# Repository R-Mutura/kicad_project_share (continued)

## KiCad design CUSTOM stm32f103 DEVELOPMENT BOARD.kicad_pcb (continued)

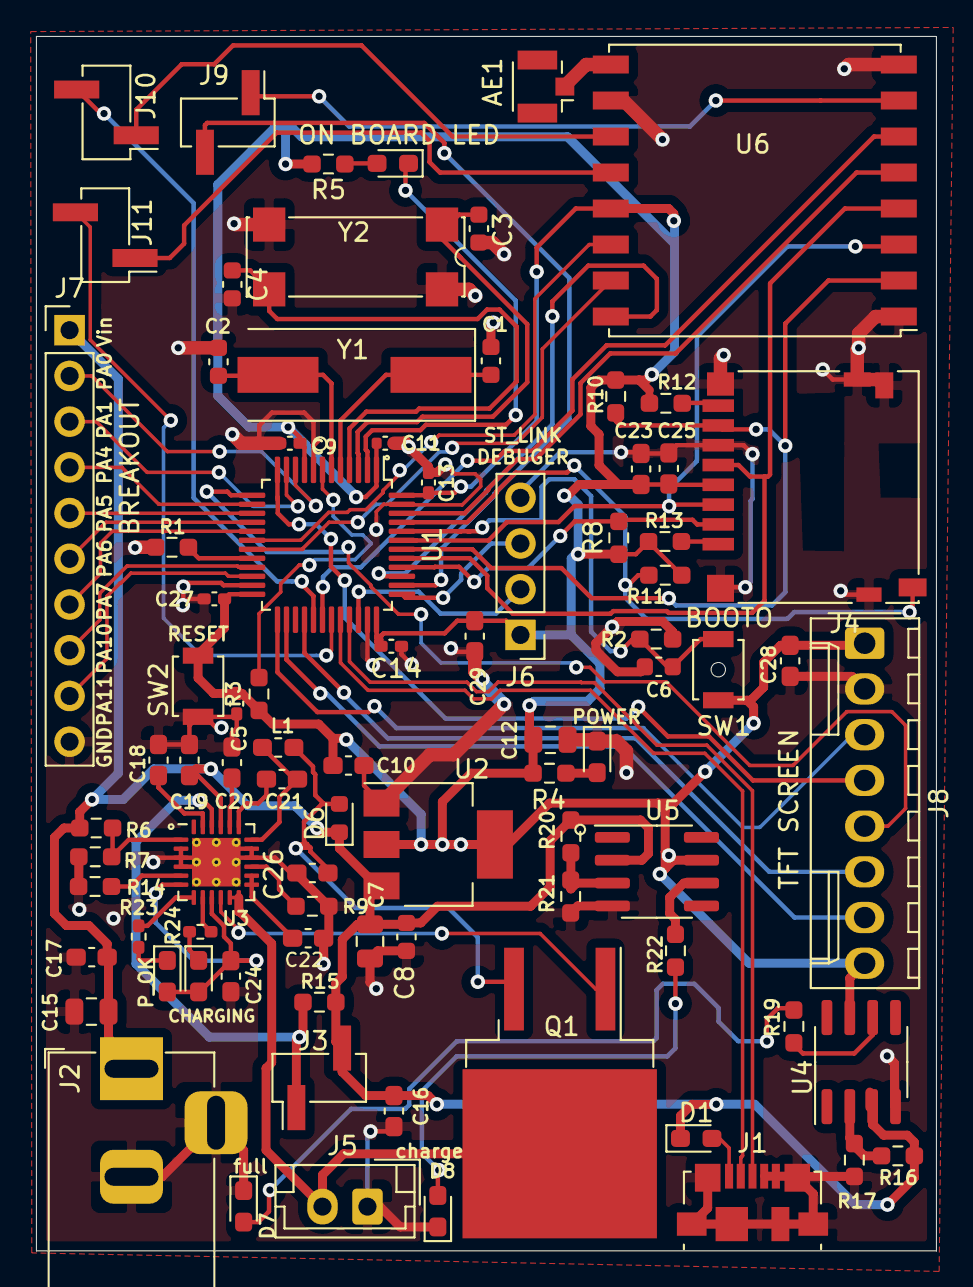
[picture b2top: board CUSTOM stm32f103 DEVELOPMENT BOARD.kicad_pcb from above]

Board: 2 copper layers, 50.0 x 67.5 mm, 84 parts (0 on the bottom side), 73 nets.

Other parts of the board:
ON BOARD LED: ON_BOARD_LED; D_0603_1608Metric_Pad1.05x0.95mm_HandSolder
POWER: POWER_LED; D_0603_1608Metric_Pad1.05x0.95mm_HandSolder

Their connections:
GND: POWER.1; also elsewhere on the board
unnamed 29: POWER.2; also elsewhere on the board
unnamed 30: ON BOARD LED.2; also elsewhere on the board
PC13: ON BOARD LED.1; also elsewhere on the board

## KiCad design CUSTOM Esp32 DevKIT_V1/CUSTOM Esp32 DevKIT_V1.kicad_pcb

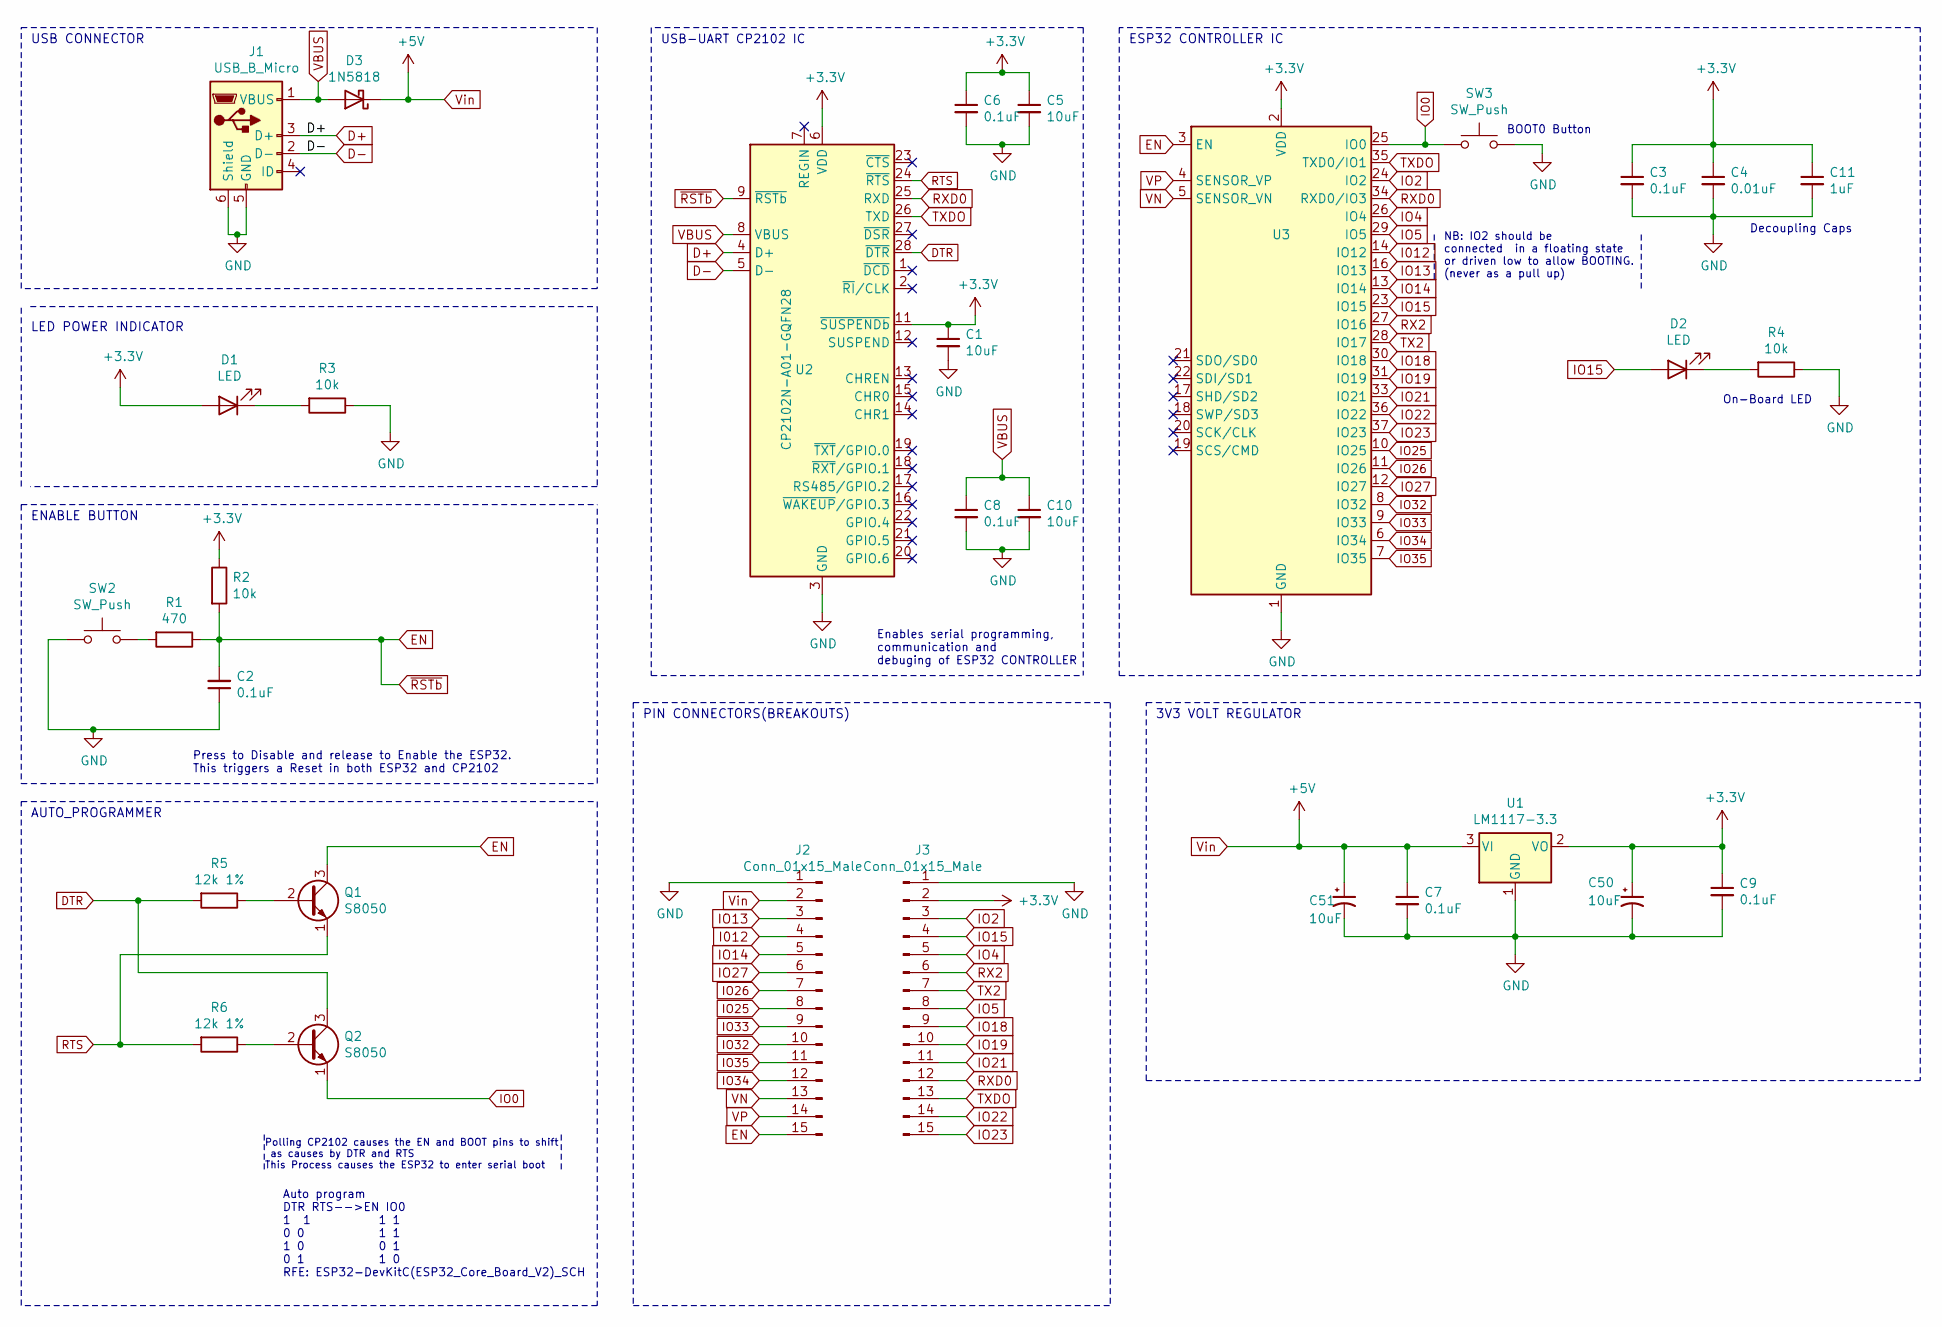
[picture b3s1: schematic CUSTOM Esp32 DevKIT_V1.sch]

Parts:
C1, C5, C10: 10uF; C_0402_1005Metric
C2, C3, C6, C7, C8, C9: 0.1uF; C_0402_1005Metric
C4: 0.01uF; C_0402_1005Metric
C11: 1uF; C_0402_1005Metric
C50, C51: 10uF; CP_EIA-1608-08_AVX-J_Pad1.25x1.05mm_HandSolder
D1, D2: LED; LED_0402_1005Metric
D3: 1N5818; D_0201_0603Metric_Pad0.64x0.40mm_HandSolder
J1: USB_B_Micro; USB_Micro-B_Molex_47346-0001
J2, J3: Conn_01x15_Male; PinHeader_1x15_P2.54mm_Vertical
Q1, Q2: S8050; TSOT-23
R1: 470; R_0402_1005Metric_Pad0.72x0.64mm_HandSolder
R2, R3, R4: 10k; R_0402_1005Metric
R5, R6: 12k 1%; R_0402_1005Metric_Pad0.72x0.64mm_HandSolder
SW2, SW3: SW_Push; SW_SPST_B3U-1000P-B
U1: LM1117-3.3; SOT-223-3_TabPin2
U2: CP2102N-A01-GQFN28; QFN-28-1EP_5x5mm_P0.5mm_EP3.35x3.35mm
U3: ESP32-WROOM-32

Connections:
+3V3: C1.1, C3.1, C4.1, C5.1, C6.1, C9.1, C11.1, C50.1, D1.2 (A), J3.2, R2.1, U1.2 (VO), U2.6 (VDD), U2.11 (~SUSPENDb), U3.2 (VDD)
D+: J1.3 (D+), U2.4 (D+)
D-: J1.2 (D-), U2.5 (D-)
DTR: Q2.3 (C), R5.2, U2.28 (~DTR)
EN: C2.2, J2.15, Q1.3 (C), R1.1, R2.2, U2.9 (~RSTb), U3.3 (EN)
GND: C1.2, C2.1, C3.2, C4.2, C5.2, C6.2, C7.2, C8.2, C9.2, C10.2, C11.2, C50.2, C51.2, J1.5 (GND), J1.6 (Shield), J2.1, J3.1, R3.1, R4.1, SW2.1, SW3.2, U1.1 (GND), U2.3 (GND), U2.29 (GND), U3.1 (GND), U3.15 (GND), U3.38 (GND), U3.39 (GND)
I012: J2.4, U3.14 (IO12)
IO0: Q2.1 (E), SW3.1, U3.25 (IO0)
IO2: J3.3, U3.24 (IO2)
IO4: J3.5, U3.26 (IO4)
IO5: J3.8, U3.29 (IO5)
IO13: J2.3, U3.16 (IO13)
IO14: J2.5, U3.13 (IO14)
IO15: D2.2 (A), J3.4, U3.23 (IO15)
IO18: J3.9, U3.30 (IO18)
IO19: J3.10, U3.31 (IO19)
IO21: J3.11, U3.33 (IO21)
IO22: J3.14, U3.36 (IO22)
IO23: J3.15, U3.37 (IO23)
IO25: J2.8, U3.10 (IO25)
IO26: J2.7, U3.11 (IO26)
IO27: J2.6, U3.12 (IO27)
IO32: J2.10, U3.8 (IO32)
IO33: J2.9, U3.9 (IO33)
IO34: J2.12, U3.6 (IO34)
IO35: J2.11, U3.7 (IO35)
unnamed: D1.1 (K), R3.2
unnamed: D2.1 (K), R4.2
unnamed: Q1.2 (B), R5.1
unnamed: Q2.2 (B), R6.1
unnamed: R1.2, SW2.2
RTS: Q1.1 (E), R6.2, U2.24 (~RTS)
RX2: J3.6, U3.27 (IO16)
RXD0: J3.12, U2.25 (RXD), U3.34 (RXD0/IO3)
TX2: J3.7, U3.28 (IO17)
TXDO: J3.13, U2.26 (TXD), U3.35 (TXD0/IO1)
VBUS: C8.1, C10.1, D3.2 (A), J1.1 (VBUS), U2.8 (VBUS)
VN: J2.13, U3.5 (SENSOR_VN)
VP: J2.14, U3.4 (SENSOR_VP)
Vin: C7.1, C51.1, D3.1 (K), J2.2, U1.3 (VI)

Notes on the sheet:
USB CONNECTOR
3V3 VOLT REGULATOR
LED POWER INDICATOR
ENABLE BUTTON
Press to Disable and release to Enable the ESP32. This triggers a Reset in both ESP32 and CP2102
PIN CONNECTORS(BREAKOUTS)
USB-UART CP2102 IC
ESP32 CONTROLLER IC
On-Board LED
Decoupling Caps
BOOT0 Button
NB: IO2 should be connected in a floating state or driven low to allow BOOTING. (never as a pull up)
Auto program DTR RTS-->EN IO0 1 1 1 1 0 0 1 1 1 0 0 1 0 1 1 0 RFE: ESP32-DevKitC(ESP32_Core_Board_V2)_SCH
Enables serial programming, communication and debuging of ESP32 CONTROLLER
AUTO_PROGRAMMER
Polling CP2102 causes the EN and BOOT pins to shift as causes by DTR and RTS This Process causes the ESP32 to enter serial boot

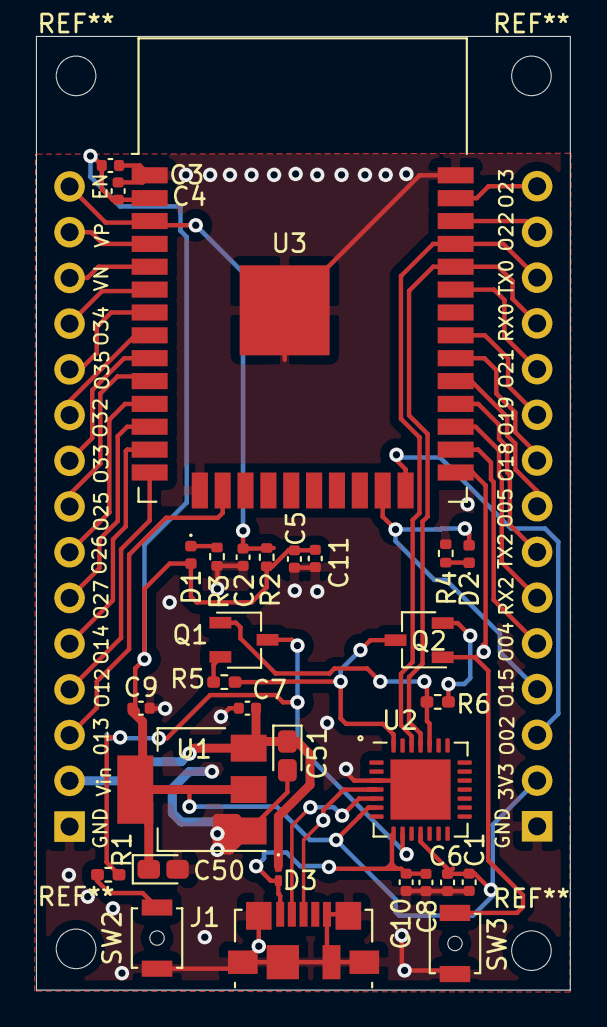
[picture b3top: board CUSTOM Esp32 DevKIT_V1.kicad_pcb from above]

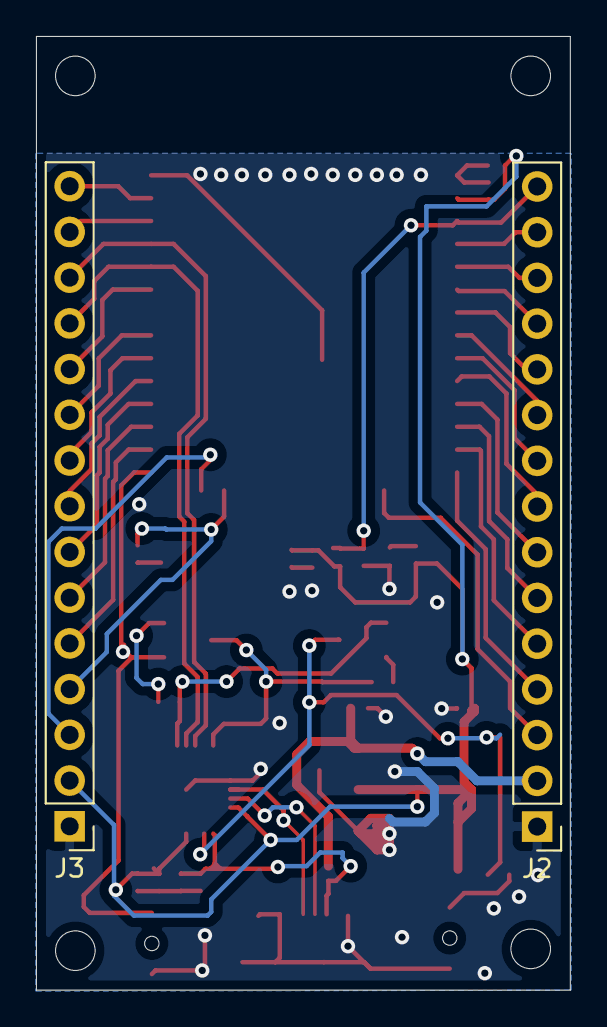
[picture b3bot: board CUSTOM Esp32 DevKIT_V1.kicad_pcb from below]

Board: 2 copper layers, 29.7 x 53.0 mm, 32 parts (2 on the bottom side), 40 nets.

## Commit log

2021-07-02 updated CUSTOM stm32f103 DEVELOPMENT BOARD
2021-07-02 Update README.md
    updated read me
2021-07-02 agriboard initial commit
